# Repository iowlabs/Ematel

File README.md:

# Ematel
Code an firwmare for ematel

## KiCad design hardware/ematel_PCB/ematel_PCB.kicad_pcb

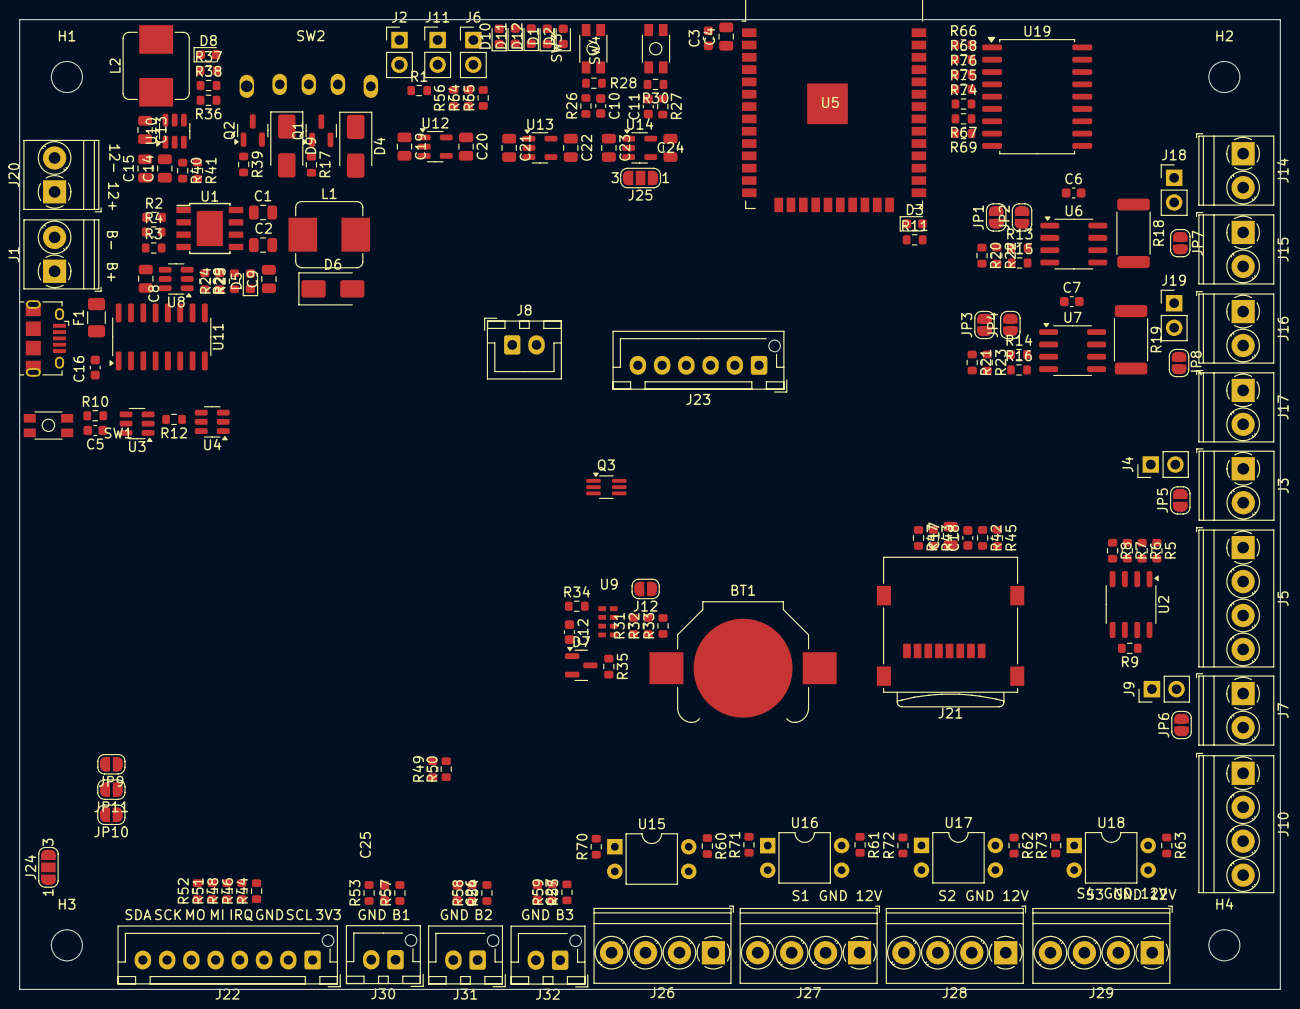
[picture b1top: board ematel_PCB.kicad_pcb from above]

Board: 2 copper layers, 130.0 x 100.0 mm, 192 parts (0 on the bottom side), 119 nets, no tracks yet.

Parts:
BT1: Battery_Cell; BatteryHolder_Keystone_3000_1x12mm
C1, C2, C4, C14, C17: 10u; C_0805_2012Metric
C3, C5, C6, C7, C10, C11, C16, C18: 100n; C_0603_1608Metric
C8, C9: 22u; C_0805_2012Metric
C12: 10n; C_0603_1608Metric
C13, C15: 0.1u; C_0805_2012Metric
C19, C20, C21, C22, C23, C24: 1u; C_0805_2012Metric
C25, C26, C27: 0.1uF; C_0603_1608Metric
D1, D2, D3, D5, D8, D10, D11, D12: LED; LED_0603_1608Metric
D4, D6, D9: D_Schottky; D_SMA
D7: BAS70-05; SOT-23
F1: FUSE; Fuse_1206_3216Metric
H1, H2, H3, H4: MountingHole; MountingHole_3.2mm_M3
J1: BAT; TerminalBlock_Phoenix_PT-1,5-2-3.5-H_1x02_P3.50mm_Horizontal
J2: V_USB; PinHeader_1x02_P2.54mm_Vertical
J3, J7, J14, J15, J16, J17: HDR-2x1; TerminalBlock_Phoenix_PT-1,5-2-3.5-H_1x02_P3.50mm_Horizontal
J4, J6, J9, J18, J19: HDR-2x1; PinHeader_1x02_P2.54mm_Vertical
J5, J10, J26, J27, J28, J29: HDR-4x1; TerminalBlock_Phoenix_PT-1,5-4-3.5-H_1x04_P3.50mm_Horizontal
J8: HDR-2x1; JST_XH_B2B-XH-A_1x02_P2.50mm_Vertical
J11: IN; PinHeader_1x02_P2.54mm_Vertical
J12: Conn_01x02; SolderJumper-2_P1.3mm_Open_RoundedPad1.0x1.5mm
J13: USB_B_Micro; USB_Micro-B_Amphenol_10118194_Horizontal
J20: IN; TerminalBlock_Phoenix_PT-1,5-2-3.5-H_1x02_P3.50mm_Horizontal
J21: Micro_SD_Card; microSD_HC_Wuerth_693072010801
J22: Conn_01x08; JST_XH_B8B-XH-AM_1x08_P2.50mm_Vertical
J23: Conn_01x08; JST_XH_B6B-XH-AM_1x06_P2.50mm_Vertical
J24, J25: HDR-3x1; SolderJumper-3_P1.3mm_Open_RoundedPad1.0x1.5mm_NumberLabels
J30, J31, J32: Conn_01x02; JST_XH_B2B-XH-AM_1x02_P2.50mm_Vertical
JP1, JP2, JP3, JP4, JP5, JP6, JP7, JP8, JP9, JP10, JP11: SolderJumper_2_Open; SolderJumper-2_P1.3mm_Open_RoundedPad1.0x1.5mm
L1: 22u; L_Bourns_SRP7028A_7.3x6.6mm
L2: 4.7u; L_Bourns_SRP7028A_7.3x6.6mm
Q1, Q2: Q_PMOS_GSD; SOT-23
Q3: Q_Dual_NPN_NPN_BRT_E1B1C2E2B2C1; SOT-363_SC-70-6_Handsoldering
R1, R12, R29, R56, R57, R58, R59, R60, R61, R62, R63, R64, R65, R70, R71, R72, R73: 1k; R_0603_1608Metric
R2: 1k2; R_0603_1608Metric
R3, R40: 12k; R_0603_1608Metric
R4, R41: 30k; R_0603_1608Metric
R5, R6, R7, R8, R13, R14, R15, R16, R17, R20, R21, R22, R23, R26, R27, R33, R34, R38, R39, R44, R49, R50, R52, R53, R54, R55, R66, R68: 10k; R_0603_1608Metric
R9: 120; R_0603_1608Metric
R10: 100; R_0603_1608Metric
R11: 330; R_0603_1608Metric
R18, R19: 16; R_2512_6332Metric
R24: 7k5; R_0603_1608Metric
R25, R37: 470; R_0603_1608Metric
R28, R30: 0; R_0603_1608Metric
R31, R32: 100k; R_0603_1608Metric
R35, R42, R43, R45, R46, R47, R48, R51, R67, R69, R74, R75, R76: 3.3k; R_0603_1608Metric
R36: 54.9k; R_0603_1608Metric
SW1, SW3, SW4: SW_DIP_x02; SMD_SWITCH
SW2: SS-12F23-G040
U1: TP4056; TP4056_SOP-8-PP
U2: MAX3485; SOP-8_3.9x4.9mm_P1.27mm
U3: DW01; SOT-23-6
U4: FS8205A; SOT-23-6
U5: ESP32-WROOM-32D; ESP32-WROOM-32
U6, U7: INA219AxD; SOIC-8_3.9x4.9mm_P1.27mm
U8: MT3608; SOT-23-6
U9: RV-8803; SON-8
U10: TPS562200; SOT-23-6
U11: CH340C; SOIC-16_3.9x9.9mm_P1.27mm
U12, U13, U14: AP2112K-3.3; SOT-23-5
U15, U16, U17, U18: PC817; DIP-4_W7.62mm
U19: MCP23008-xSO; SOIC-18W_7.5x11.6mm_P1.27mm

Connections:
12V_IN: J4.1, J9.1, J18.1, J19.1
420_VDD_ch1: J16.1, J19.2, R19.1, U7.8 (IN+)
420_VDD_ch2: J14.1, J18.2, R18.1, U6.8 (IN+)
420_VSS_ch1: J16.2, J17.2, JP8.2 (B)
420_VSS_ch2: J14.2, J15.2, JP7.2 (B)
420_sens_ch1+: J17.1, R19.2, U7.7 (IN-)
420_sens_ch2+: J15.1, R18.2, U6.7 (IN-)
485_RX: R8.2, U2.4 (DI), U5.28 (IO17)
485_TX: R5.2, U2.1 (RO), U5.27 (IO16)
+3V3: C3.1, C4.1, C6.1, C7.1, C16.1, C20.1, D7.1 (A), D7.2 (A), J22.1, J23.1, JP1.2 (B), JP2.2 (B), JP3.2 (B), JP4.2 (B), JP9.1 (A), JP10.1 (A), JP11.1 (A), R13.1, R14.1, R15.1, R16.1, R26.1, R27.1, R31.1, R32.1, R33.1, R34.1, R53.1, R54.1, R55.1, R56.1, R60.1, R61.1, R62.1, R63.1, R67.2, R69.2, U5.2 (VDD), U6.5 (VS), U7.5 (VS), U11.4 (V3), U11.16 (VCC), U12.5 (VOUT), U19.18 (VDD)
+5V: C19.1, C21.1, C23.1, J24.1, J25.1, SW2.2 (B), U12.1 (VIN), U12.3 (EN), U13.1 (VIN), U14.1 (VIN)
/BAT+: C2.1, C8.1, J1.1, L1.1, R3.2, R10.1, U1.5 (BAT), U8.4 (EN), U8.5 (IN)
/BAT-: C5.2, J1.2, SW1.3, SW1.4, U3.6 (GND), U4.1 (S1)
/CS: R12.2, U3.2 (CS)
/EN_VDL_S: J25.2, U13.3 (EN)
/EN_VS_S: J24.2, U14.3 (EN)
/EVI: J12.1, R32.2, U9.7 (EVI)
/FB_5V: R24.2, R29.1, U8.3 (FB)
/INT: R31.2, U9.6 (!INT)
/OC: U3.3 (OC), U4.4 (G2)
/OD: U3.1 (OD), U4.6 (G1)
/SW_5V: D6.2 (A), L1.2, U8.1 (SW)
/VRFID_3V3: C24.1, R65.1, U14.5 (VOUT)
/VS_3V3: R5.1, R6.1, R7.1, R8.1, U2.8 (VCC)
/V_USB: D9.2 (A), F1.2, Q2.1 (G), R39.1
/V_in: F1.1, J13.1 (VBUS)
/Vpre_5V: C1.1, D4.2 (A), D9.1 (K), J2.1, Q1.1 (G), Q2.2 (S), R1.1, R17.1, U1.4 (Vcc), U1.8 (CE)
A0: JP9.2 (B), R74.2, U19.5 (A0)
A1: JP10.2 (B), R75.2, U19.4 (A1)
A2: JP11.2 (B), R76.2, U19.3 (A2)
BAT_LVL: R3.1, R4.1, U5.5 (SENSOR_VN)
DTR#: Q3.4 (E1), R49.1, U11.13 (~DTR)
GND: BT1.2 (-), C1.2, C2.2, C3.2, C4.2, C6.2, C7.2, C8.2, C9.2, C10.2, C11.2, C12.2, C14.2, C15.2, C16.2, C17.2, C18.2, C19.2, C20.2, C21.2, C22.2, C23.2, C24.2, C25.2, C26.2, C27.2, D3.1 (K), D5.1 (K), D8.1 (K), D10.1 (K), D11.1 (K), D12.1 (K), J2.2, J6.2, J8.2, J11.2, J12.2, J13.5 (GND), J13.6 (Shield), J20.2, J21.6 (VSS), J21.9 (SHIELD), J22.3, J23.2, J26.2, J27.2, J28.2, J29.2, J30.2, J31.2, J32.2, JP5.2 (B), JP6.2 (B), JP7.1 (A), JP8.1 (A), R2.1, R4.2, R12.1, R17.2, R20.2, R21.2, R22.2, R23.2, R29.2, R38.2, R39.2, R41.2, R74.1, R75.1, R76.1, SW1.1, SW1.2, SW2.3 (C), SW2.4, SW3.1, SW3.2, SW4.1, SW4.2, U1.1 (TEMP), U1.3 (GND), U2.5 (GND), U4.3 (S2), U5.1 (GND), U5.15 (GND), U5.38 (GND), U5.39 (GND), U6.6 (GND), U7.6 (GND), U8.2 (GND), U9.4 (CLKOE), U9.5 (VSS), U10.1 (GND), U11.1 (GND), U12.2 (GND), U13.2 (GND), U14.2 (GND), U15.2, U15.3, U16.2, U16.3, U17.2, U17.3, U18.2, U18.3, U19.9 (VSS)
GPA0: C25.1, R53.2, R57.2, U19.10 (GP0)
GPA1: C26.1, R54.2, R58.2, U19.11 (GP1)
GPA2: C27.1, R55.2, R59.2, U19.12 (GP2)
GPA4: J23.3, U19.14 (GP4)
GPA5: J23.4, U19.15 (GP5)
GPA6: J23.5, U19.16 (GP6)
GPA7: J23.6, U19.17 (GP7)
INTA: R69.1, U19.8 (INT)
IO0: C10.1, Q3.3 (C1), R26.2, R28.1, U5.25 (IO0)
IO2: R11.1, U5.24 (IO2)
MCP_RESET: R67.1, U19.6 (~RESET)
unnamed: BT1.1 (+), R35.2
unnamed: D1.2 (A), D2.2 (A), R1.2
unnamed: D1.1 (K), U1.7 (~CHRG)
unnamed: D2.1 (K), U1.6 (~STDBY)
unnamed: D3.2 (A), R11.2
unnamed: D4.1 (K), Q1.2 (S), SW2.1 (A)
unnamed: D5.2 (A), R25.2
unnamed: C12.1, D7.3 (K), R35.1, U9.3 (VDD)
unnamed: D8.2 (A), R37.2
unnamed: D10.2 (A), R56.2
unnamed: D11.2 (A), R64.2
unnamed: D12.2 (A), R65.2
unnamed: J13.3 (D+), U11.5 (UD+)
unnamed: J13.2 (D-), U11.6 (UD-)
unnamed: J21.5 (CLK), R43.2
unnamed: J21.3 (CMD), R42.2
unnamed: J21.7 (DAT0), R47.2
unnamed: J21.2 (DAT3/CD), R45.2
unnamed: J22.2, R44.1
unnamed: J22.5, R46.1
unnamed: J22.6, R48.1
unnamed: J22.7, R51.1
unnamed: J22.8, R52.1
unnamed: J30.1, R57.1
unnamed: J31.1, R58.1
unnamed: J32.1, R59.1
unnamed: JP1.1 (A), R20.1, U6.2 (A0)
unnamed: JP2.1 (A), R22.1, U6.1 (A1)
unnamed: JP3.1 (A), R21.1, U7.2 (A0)
unnamed: JP4.1 (A), R23.1, U7.1 (A1)
unnamed: Q3.5 (B1), R50.1
unnamed: Q3.2 (B1), R49.2
unnamed: R28.2, SW3.3, SW3.4
unnamed: R30.2, SW4.3, SW4.4
unnamed: R70.2, U15.1
unnamed: R71.2, U16.1
unnamed: R72.2, U17.1
unnamed: R73.2, U18.1
unnamed: R2.2, U1.2 (PROG)
unnamed: C5.1, R10.2, U3.5 (VCC)
unnamed: C13.2, L2.1, U10.2 (SW)
unnamed: C13.1, U10.6 (VBST)
unnamed: R36.1, U10.4 (VFB)
unnamed: R66.2, U19.1 (SCL)
unnamed: R68.2, U19.2 (SDA)
RESET: C11.1, J8.1, Q3.6 (C1), R27.2, R30.1, U5.3 (EN)
RS485_A_ch2: J5.3, J10.3, R9.2, U2.6 (A)
RS485_B_ch2: J5.4, J10.4, R9.1, U2.7 (B)
RS485_EN: R6.2, R7.2, U2.2 (~RE), U2.3 (DE), U5.23 (IO15)
RS485_VDD_aux: J7.1, J9.2, J10.1
RS485_VDD_ch2: J3.1, J4.2, J5.1
RS485_VSS_aux: J7.2, J10.2, JP6.1 (A)
RS485_VSS_ch2: J3.2, J5.2, JP5.1 (A)
RST#: Q3.1 (E1), R50.2, U11.14 (~RTS)
RX: U5.34 (RXD0/IO3), U11.2 (TXD)
S1_IN: J26.3, R70.1
S2_IN: J27.3, R71.1
S3_IN: J28.3, R72.1
S4_IN: J29.3, R73.1
SCL: R15.2, R16.2, R33.2, R44.2, R66.1, U5.36 (IO22), U6.4 (SCL), U7.4 (SCL), U9.8 (SCL)
SDA: R13.2, R14.2, R34.2, R52.2, R68.1, U5.33 (IO21), U6.3 (SDA), U7.3 (SDA), U9.1 (SDA)
SD_CS: R45.1, U5.29 (IO5)
SENSOR 1: R60.2, U5.26 (IO4), U15.4
SENSOR 2: R61.2, U16.4, U19.13 (GP3)
SENSOR 3: R62.2, U5.6 (IO34), U17.4
SENSOR 4: R63.2, U5.7 (IO35), U18.4
SPI1_CLK: R43.1, R51.2, U5.30 (IO18)
SPI1_MISO: R46.2, R47.1, U5.31 (IO19)
SPI1_MOSI: R42.1, R48.2, U5.37 (IO23)
TX: U5.35 (TXD0/IO1), U11.3 (RXD)
VDL_3V3: C17.1, C18.1, C22.1, J21.4 (VDD), R64.1, U13.5 (VOUT)
VIN_5V: J11.1, L2.2, Q2.3 (D), R36.2, R37.1, R38.1
VIN_12V: C14.1, C15.1, J20.1, J26.1, J27.1, J28.1, J29.1, R40.2, U10.3 (VIN), U10.5 (EN)
V_AUTO_LVL: R40.1, R41.1, U5.4 (SENSOR_VP)
Vbat_5V: C9.1, D6.1 (K), J6.1, Q1.3 (D), R24.1, R25.1

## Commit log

2024-03-07 first version. pub to two mqtt brokeres and save to local mysql db
2024-04-12 PCB update
2024-04-17 Update PCB (Finish(?))
2024-04-17 PCB Update, layout begin
2024-05-02 'simulacion'
2024-05-04 simulation
2024-05-06 Actualizacion PCB
2024-06-13 adding codes
2024-06-13 adding temporis web
